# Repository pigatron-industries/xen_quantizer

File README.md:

# Quantizer

A Eurorack quantizer module

[Documentation](https://pigatron-industries.github.io/xen_quantizer/)

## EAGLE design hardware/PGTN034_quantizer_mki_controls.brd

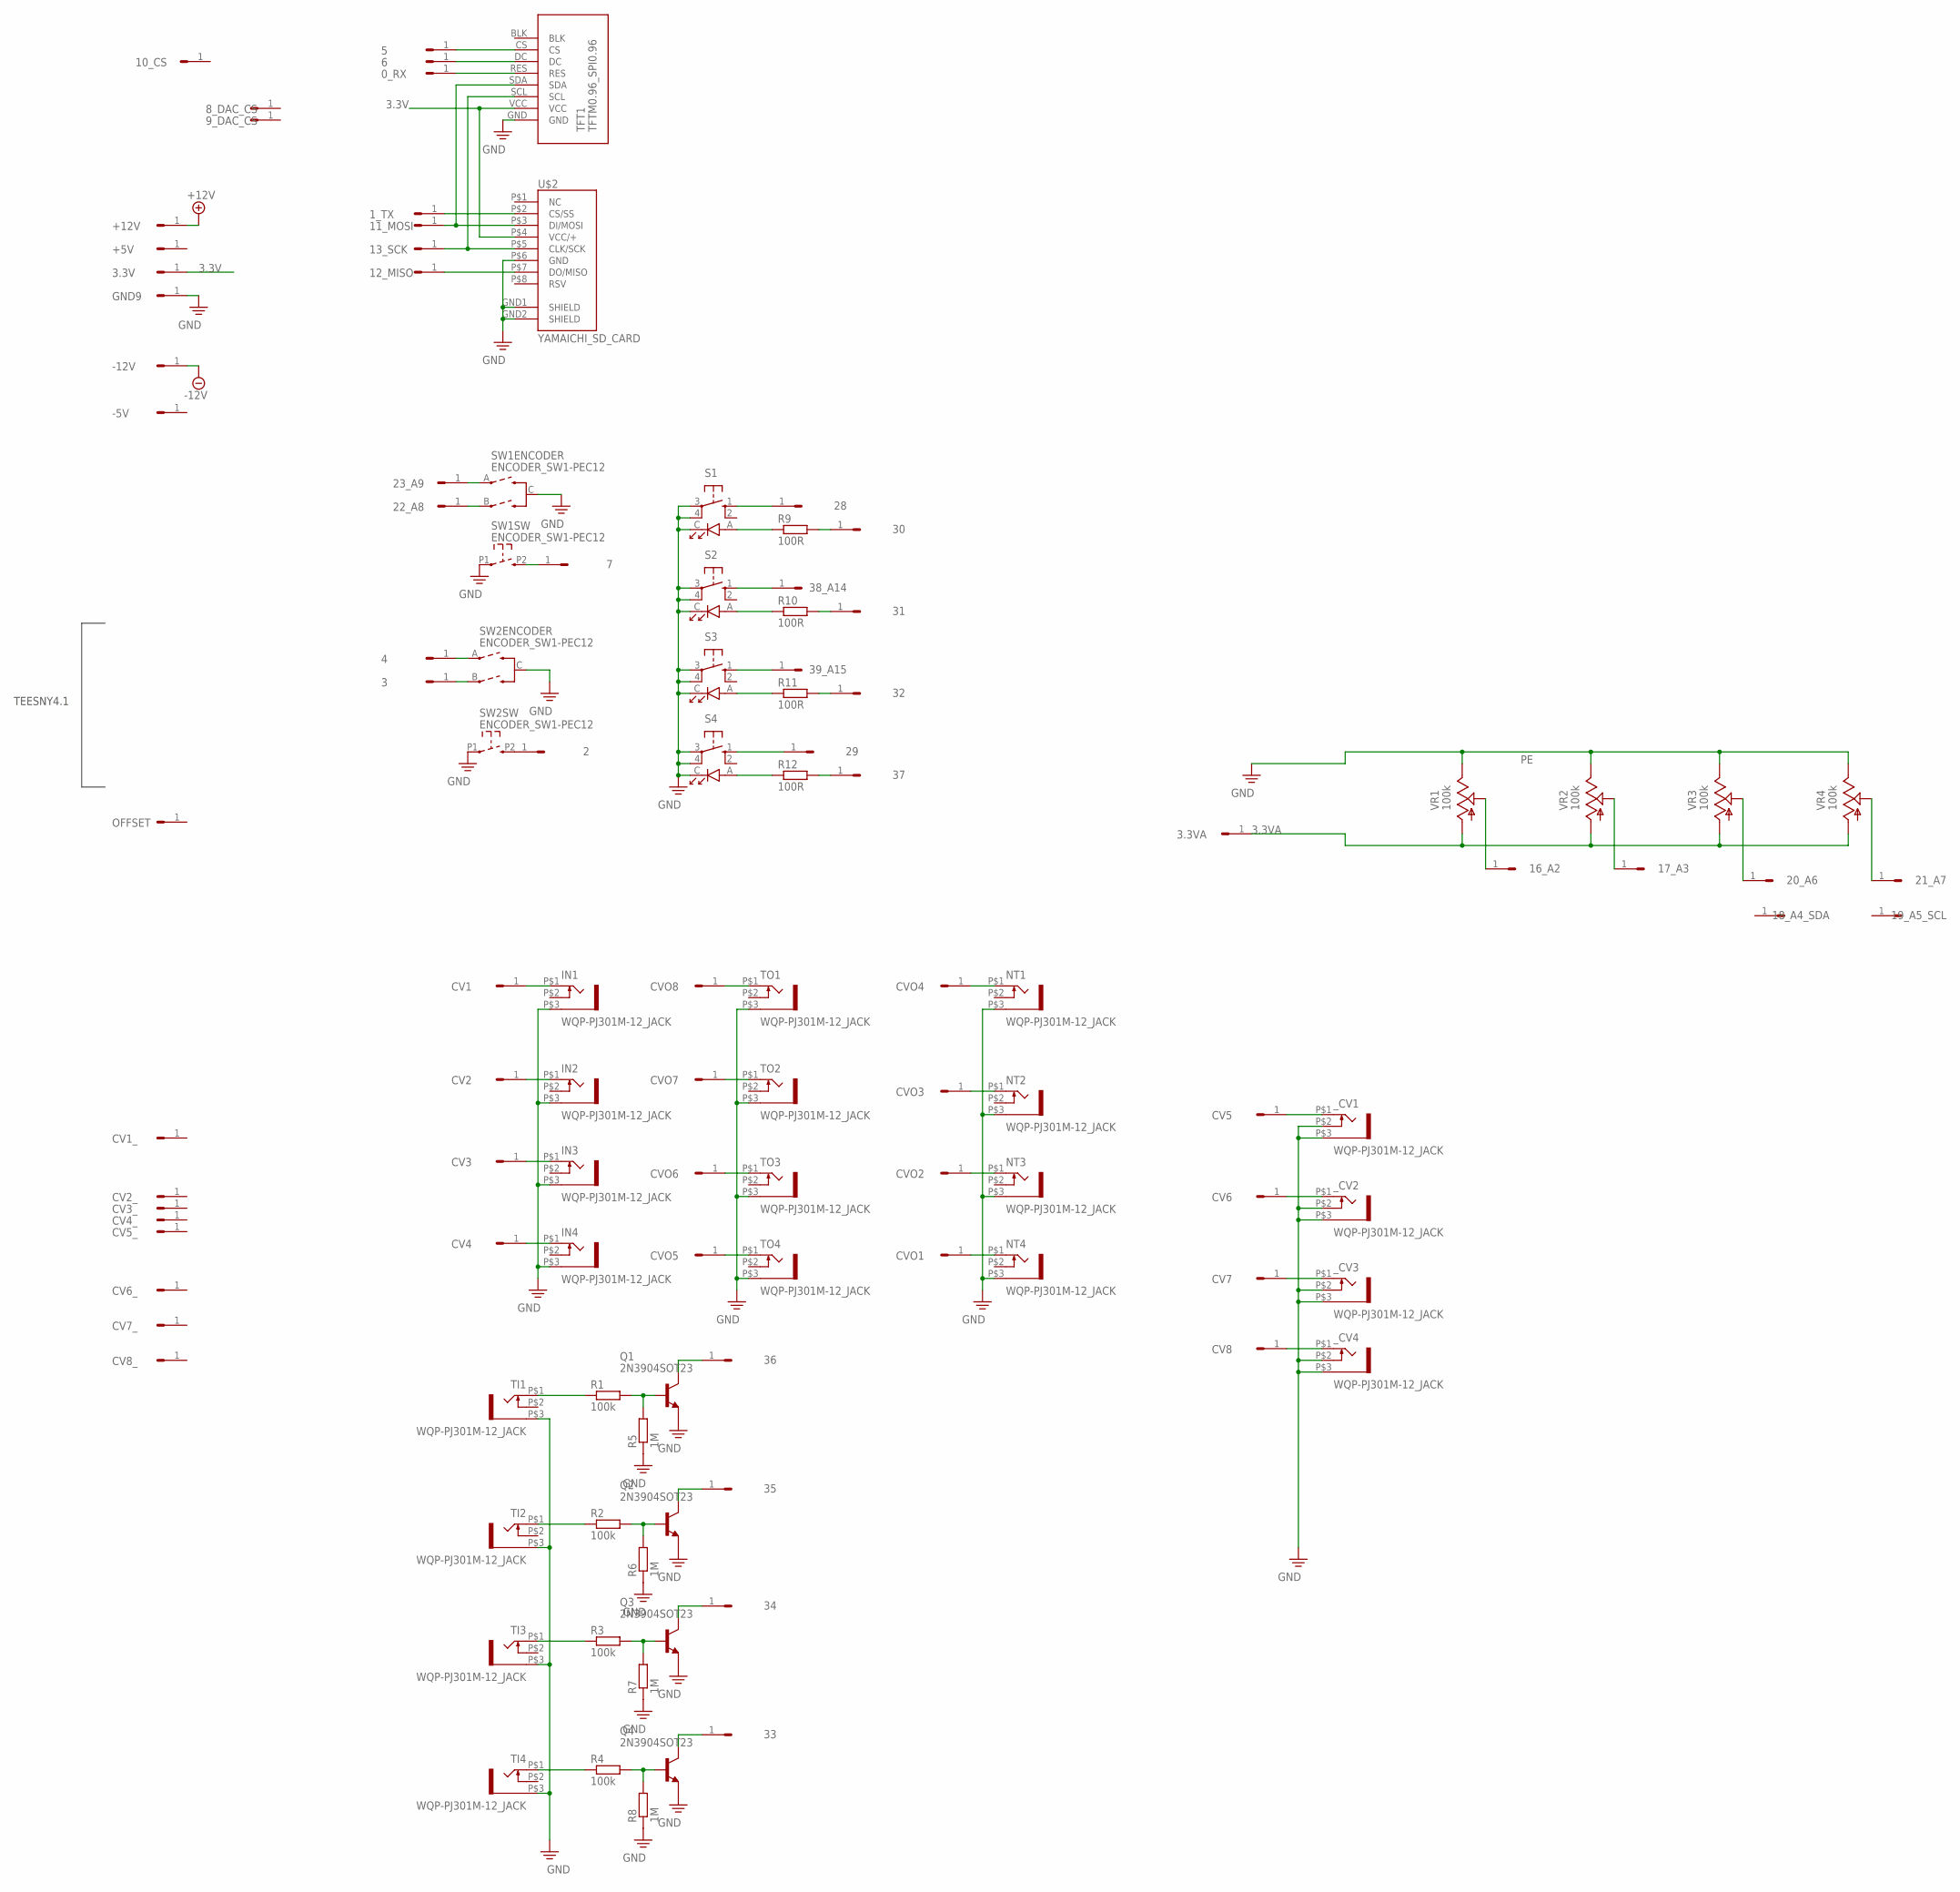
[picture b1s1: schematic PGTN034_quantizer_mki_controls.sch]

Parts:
0_RX, 1_TX, 2, 3, 3.3V, 3.3VA, 4, 5, 6, 7, 8_DAC_CS, 9_DAC_CS, 10_CS, 11_MOSI, 12_MISO, 13_SCK, 16_A2, 17_A3, 18_A4_SDA, 19_A5_SCL, 20_A6, 21_A7, 22_A8, 23_A9, 28, 29, 30, 31, 32, 33, 34, 35, 36, 37, 38_A14, 39_A15: HEADER/MALE/01
+5V, +12V: HEADER/MALE/01
-5V, -12V: HEADER/MALE/01
CV1, CV1_, CV2, CV2_, CV3, CV3_, CV4, CV4_, CV5, CV5_, CV6, CV6_, CV7, CV7_, CV8, CV8_: HEADER/MALE/01
CVO1, CVO2, CVO3, CVO4, CVO5, CVO6, CVO7, CVO8: HEADER/MALE/01
GND9: HEADER/MALE/01
IN1, IN2, IN3, IN4: WQP-PJ301M-12_JACK
NT1, NT2, NT3, NT4: WQP-PJ301M-12_JACK
OFFSET: HEADER/MALE/01
Q1, Q2, Q3, Q4: 2N3904SOT23; SOT23
R1, R2, R3, R4: 100k; R0603
R5, R6, R7, R8: 1M; R0603
R9, R10, R11, R12: 100R; R0603
S1, S2, S3, S4: SW-LEDTHONK; SW-PUSH-TACT-LED-THONK
SW1, SW2: ENCODER_SW1-PEC12; PEC12_INCREMENTAL_ENCODER
TFT1: TFTM0.96_SPI0.96; TFTM0.96
TI1, TI2, TI3, TI4: WQP-PJ301M-12_JACK
TO1, TO2, TO3, TO4: WQP-PJ301M-12_JACK
U$2: YAMAICHI_SD_CARD; YAMAICHI_MICROSD_VERTICAL
VR1, VR2, VR3, VR4: 100k; 9MM_SNAP-IN_POT
_CV1, _CV2, _CV3, _CV4: WQP-PJ301M-12_JACK

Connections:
3.3V: 3.3V.1, TFT1.VCC, U$2.P$4 (VCC/+)
3.3VA: 3.3VA.1, VR1.1 (A), VR2.1 (A), VR3.1 (A), VR4.1 (A)
+12V: +12V.1
-12V: -12V.1
unnamed: CV5.1, _CV1.P$1 (2)
unnamed: 16_A2.1, VR1.2 (S)
unnamed: CV6.1, _CV2.P$1 (2)
unnamed: 0_RX.1, TFT1.RES
unnamed: CVO1.1, NT4.P$1 (2)
unnamed: CVO2.1, NT3.P$1 (2)
unnamed: 17_A3.1, VR2.2 (S)
unnamed: CVO3.1, NT2.P$1 (2)
unnamed: 20_A6.1, VR3.2 (S)
unnamed: 21_A7.1, VR4.2 (S)
unnamed: CVO4.1, NT1.P$1 (2)
unnamed: CVO5.1, TO4.P$1 (2)
unnamed: CVO6.1, TO3.P$1 (2)
unnamed: CVO7.1, TO2.P$1 (2)
unnamed: CVO8.1, TO1.P$1 (2)
unnamed: CV1.1, IN1.P$1 (2)
unnamed: CV2.1, IN2.P$1 (2)
unnamed: CV3.1, IN3.P$1 (2)
unnamed: CV4.1, IN4.P$1 (2)
unnamed: CV7.1, _CV3.P$1 (2)
unnamed: CV8.1, _CV4.P$1 (2)
unnamed: R1.1, TI1.P$1 (2)
unnamed: R2.1, TI2.P$1 (2)
unnamed: R3.1, TI3.P$1 (2)
unnamed: R4.1, TI4.P$1 (2)
unnamed: Q1.1 (B), R1.2, R5.2
unnamed: Q2.1 (B), R2.2, R6.2
unnamed: Q3.1 (B), R3.2, R7.2
unnamed: Q4.1 (B), R4.2, R8.2
unnamed: 36.1, Q1.3 (C)
unnamed: 35.1, Q2.3 (C)
unnamed: 34.1, Q3.3 (C)
unnamed: 33.1, Q4.3 (C)
unnamed: R9.1, S1.A
unnamed: R12.1, S4.A
unnamed: 7.1, SW1.P2 (2)
unnamed: 23_A9.1, SW1.A
unnamed: 22_A8.1, SW1.B
unnamed: R11.1, S3.A
unnamed: R10.1, S2.A
unnamed: 28.1, S1.1 (S)
unnamed: 38_A14.1, S2.1 (S)
unnamed: 39_A15.1, S3.1 (S)
unnamed: 29.1, S4.1 (S)
unnamed: 31.1, R10.2
unnamed: 30.1, R9.2
unnamed: 32.1, R11.2
unnamed: 37.1, R12.2
unnamed: 12_MISO.1, U$2.P$7 (DO/MISO)
unnamed: 11_MOSI.1, TFT1.SDA, U$2.P$3 (DI/MOSI)
unnamed: 13_SCK.1, TFT1.SCL, U$2.P$5 (CLK/SCK)
unnamed: 5.1, TFT1.CS
unnamed: 6.1, TFT1.DC
unnamed: 3.1, SW2.B
unnamed: 4.1, SW2.A
unnamed: 2.1, SW2.P2 (2)
unnamed: 1_TX.1, U$2.P$2 (CS/SS)
PE: GND9.1, IN1.P$3 (1), IN2.P$3 (1), IN3.P$3 (1), IN4.P$3 (1), NT1.P$3 (1), NT2.P$3 (1), NT3.P$3 (1), NT4.P$3 (1), Q1.2 (E), Q2.2 (E), Q3.2 (E), Q4.2 (E), R5.1, R6.1, R7.1, R8.1, S1.3, S1.4 (P1), S1.C, S2.3, S2.4 (P1), S2.C, S3.3, S3.4 (P1), S3.C, S4.3, S4.4 (P1), S4.C, SW1.C, SW1.P1 (1), SW2.C, SW2.P1 (1), TFT1.GND, TI1.P$3 (1), TI2.P$3 (1), TI3.P$3 (1), TI4.P$3 (1), TO1.P$3 (1), TO2.P$3 (1), TO3.P$3 (1), TO4.P$3 (1), U$2.GND1 (SHIELD), U$2.GND2 (SHIELD), U$2.P$6 (GND), VR1.3 (E), VR2.3 (E), VR3.3 (E), VR4.3 (E), _CV1.P$2 (3), _CV1.P$3 (1), _CV2.P$2 (3), _CV2.P$3 (1), _CV3.P$2 (3), _CV3.P$3 (1), _CV4.P$2 (3), _CV4.P$3 (1)

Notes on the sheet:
TEESNY4.1

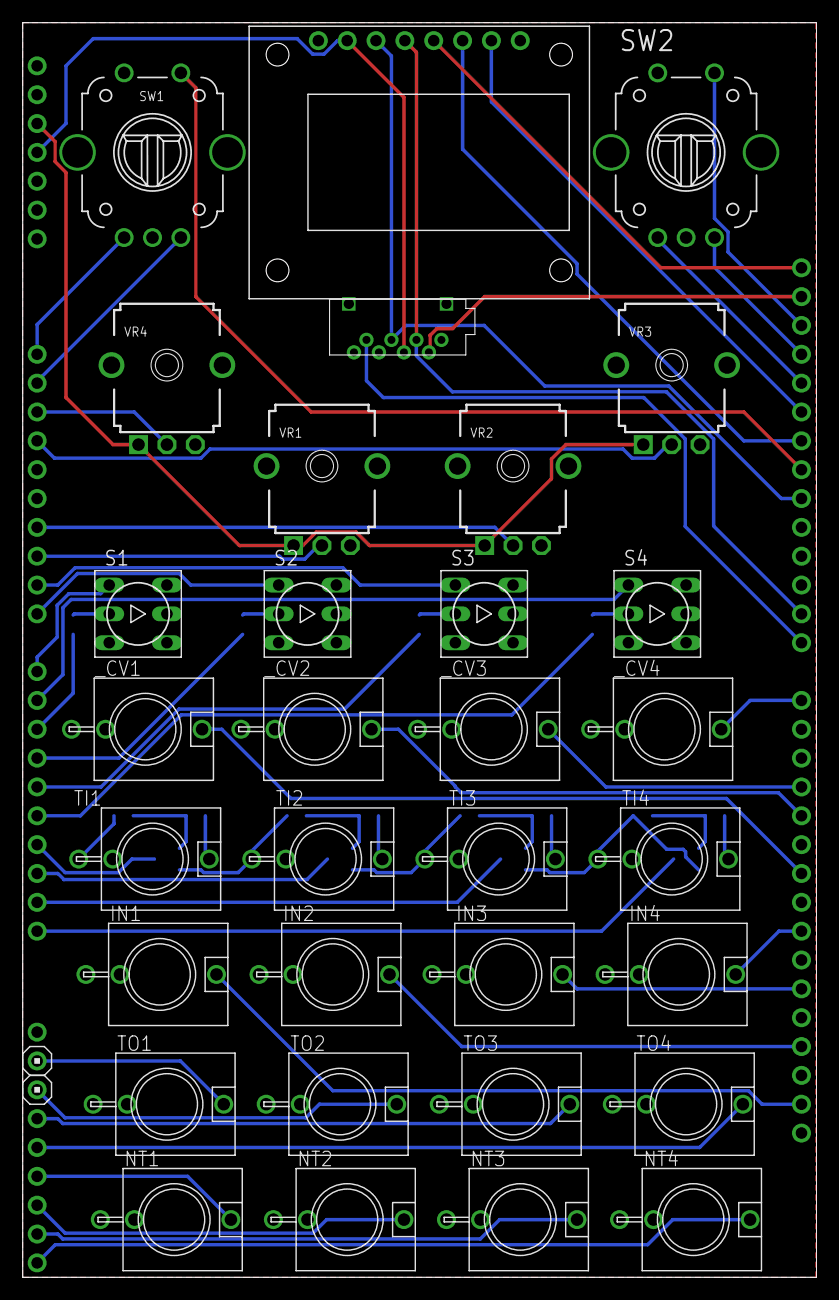
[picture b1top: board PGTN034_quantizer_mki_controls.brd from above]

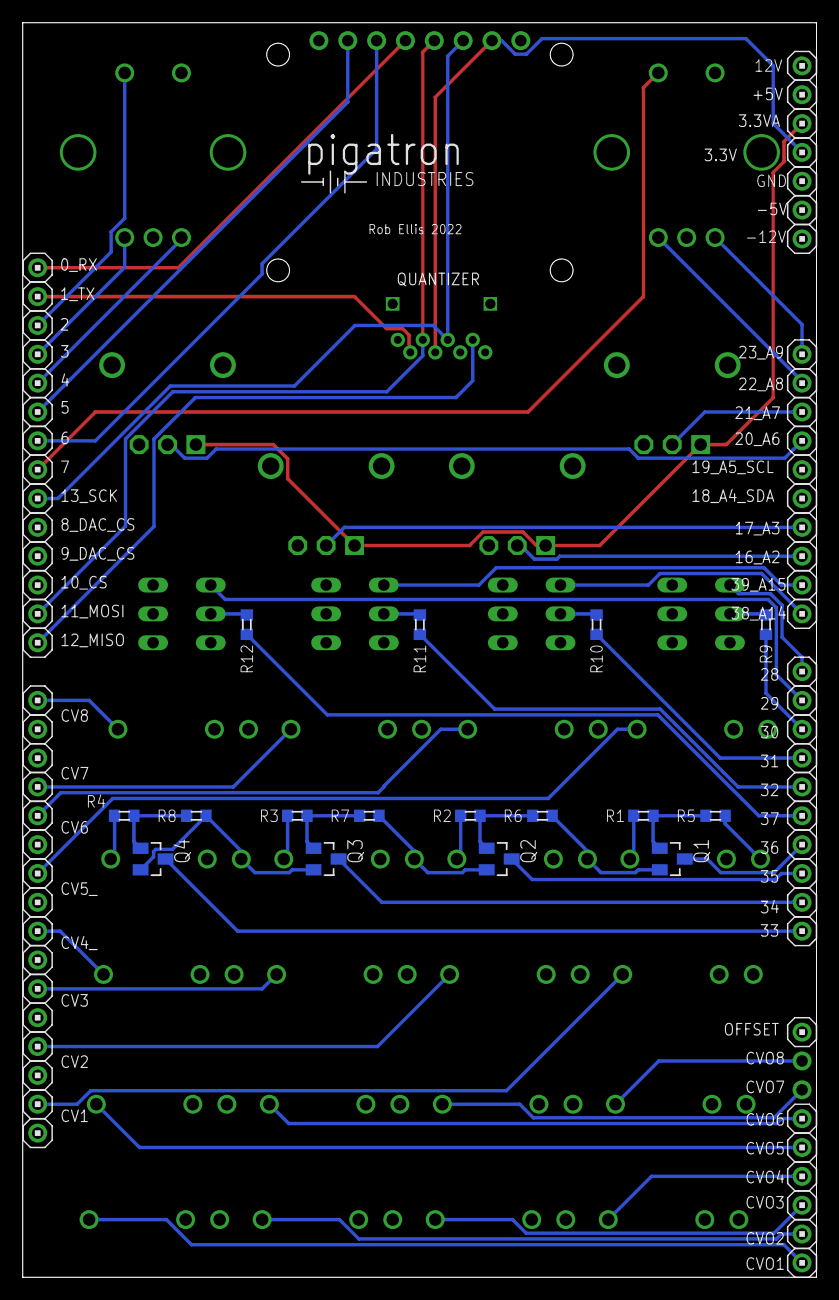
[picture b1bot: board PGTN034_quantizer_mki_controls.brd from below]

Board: 2 copper layers, 69.9 x 110.5 mm, 115 parts (81 on the bottom side), 60 nets.

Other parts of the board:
U$1: PIGATRON-LOGO

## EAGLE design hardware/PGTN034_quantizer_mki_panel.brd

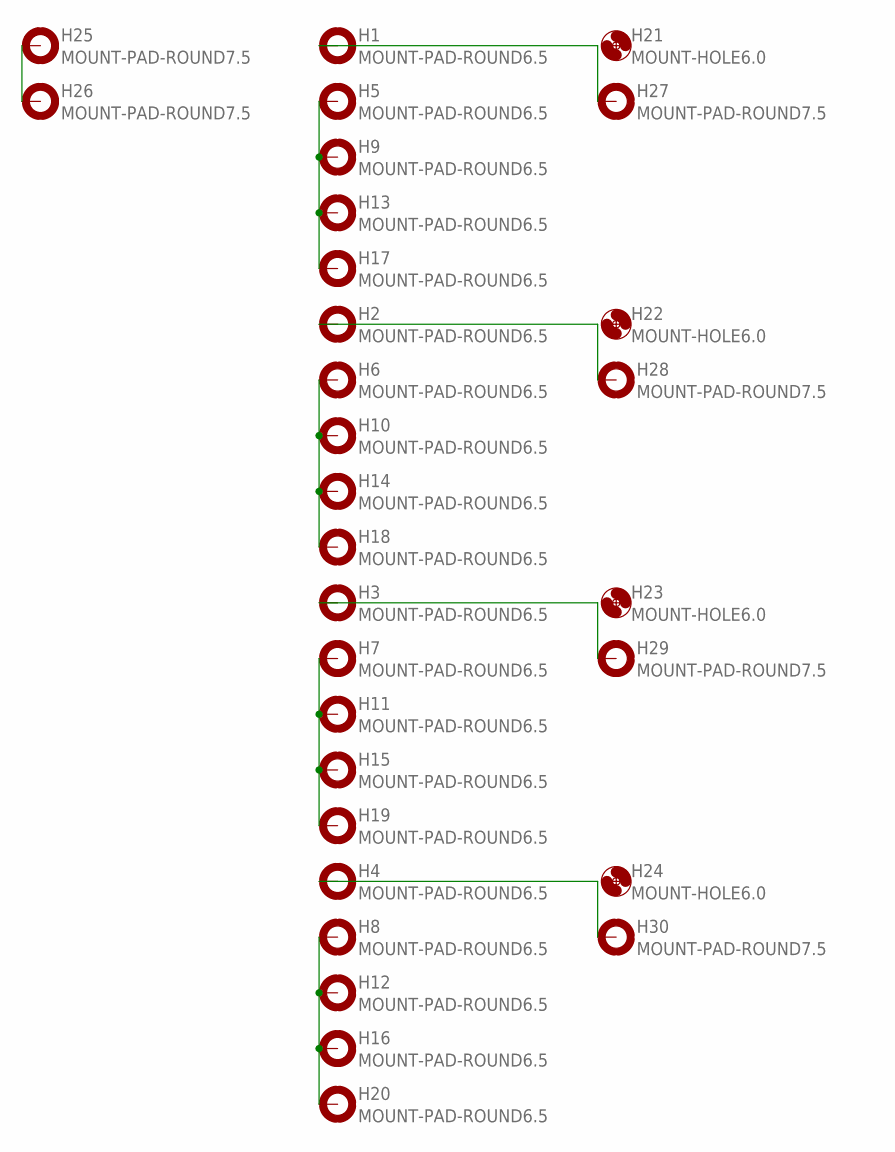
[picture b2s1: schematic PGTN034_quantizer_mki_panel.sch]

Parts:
H1, H2, H3, H4, H5, H6, H7, H8, H9, H10, H11, H12, H13, H14, H15, H16, H17, H18, H19, H20: MOUNT-PAD-ROUND6.5; 6.5-PAD
H21, H22, H23, H24: MOUNT-HOLE6.0; 6,0
H25, H26, H27, H28, H29, H30: MOUNT-PAD-ROUND7.5; 7.5-PAD

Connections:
unnamed: H5.B6.5, H9.B6.5, H13.B6.5, H17.B6.5
unnamed: H6.B6.5, H10.B6.5, H14.B6.5, H18.B6.5
unnamed: H7.B6.5, H11.B6.5, H15.B6.5, H19.B6.5
unnamed: H8.B6.5, H12.B6.5, H16.B6.5, H20.B6.5
unnamed: H2.B6.5, H28.B7.5
unnamed: H3.B6.5, H29.B7.5
unnamed: H4.B6.5, H30.B7.5
unnamed: H25.B7.5, H26.B7.5
unnamed: H1.B6.5, H27.B7.5

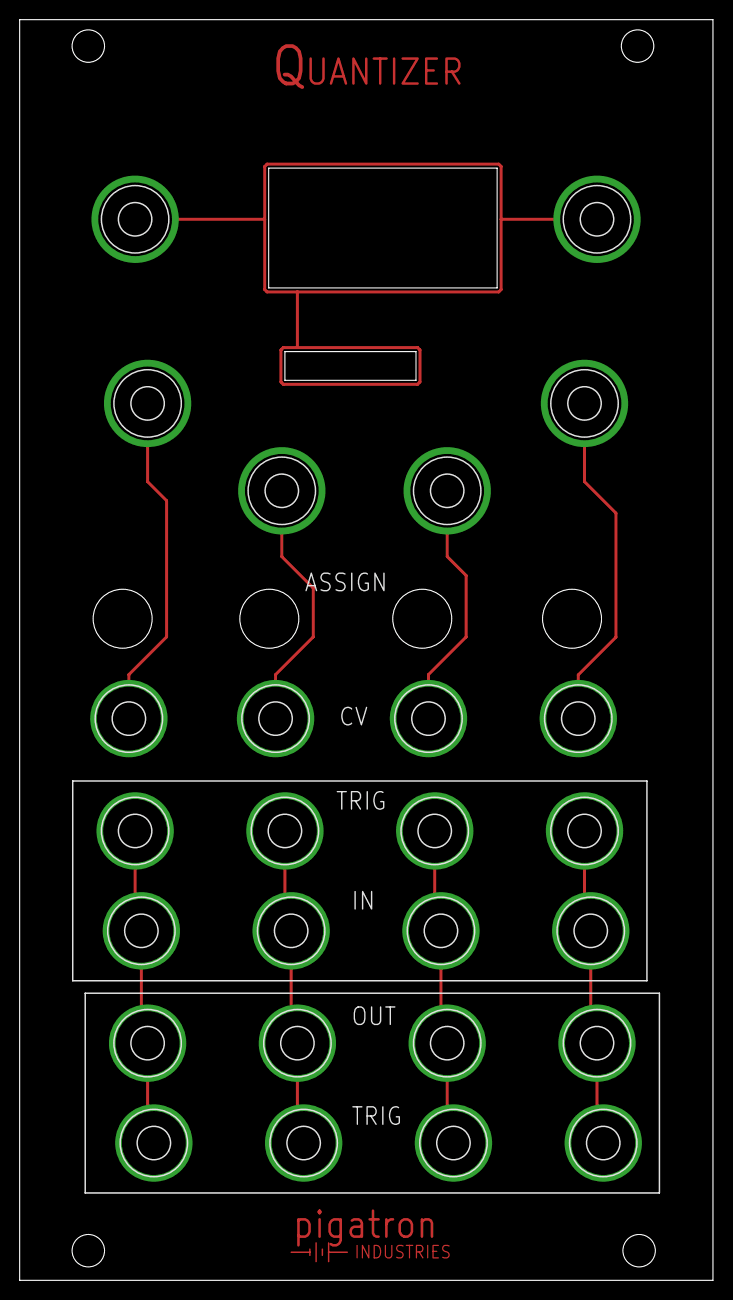
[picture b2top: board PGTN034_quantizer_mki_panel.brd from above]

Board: 2 copper layers, 70.5 x 128.3 mm, 35 parts (0 on the bottom side), 9 nets.

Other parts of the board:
U$2: PIGATRON-LOGO-TRACE
U$3, U$4, U$5, U$6: 3,3

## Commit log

2022-04-25 initial code commit
2022-04-26 hardware and controller
2022-04-26 re-order pins + add MCP23S17
2022-04-29 Pitch quantizer
2022-05-01 add library.json to use as library
2022-05-01 added tuning
2022-05-01 rename to tuning
2022-05-01 correct srcDir
2022-05-01 name changes
2022-05-01 Removed note from quantizer
2022-05-02 Renamed some types
2022-05-03 scale repository
2022-05-04 manage links between scales and chords
2022-05-07 Tuning mode to help with oscilaltor tuning
2022-05-07 ignore compiled python files
2022-05-10 Python code to visualise scales
2022-05-12 rename
2022-05-12 plot notes
2022-05-13 repeat modes and scales
2022-05-13 More text
2022-05-13 convert script
2022-05-13 use mathjax
2022-05-20 Added polar plots
2022-05-20 Added polar plots of scales and chords
2022-05-21 Chord quality selected by scale
2022-05-21 Scale offset pot
2022-05-22 Fixed quantizer bugs and added tests
2022-05-23 added chord tests
2022-05-23 Fix offset scale chords
2022-05-24 title
2022-05-26 Simplified scale offsets
2022-05-27 moved py files to lib folder
2022-05-27 clear outputs
2022-05-27 harmonics
2022-05-27 harmonics plot changes
2022-05-28 rename PitchQuantizer
2022-05-29 python changes
2022-05-29 Quantize to current chord
2022-05-29 set chord in init
2022-05-31 add dissonance rating to intervals
2022-06-01 Add offset in quantizeToChord
2022-06-04 Refactor
2022-06-05 Moved tuning data out of controllers
2022-06-07 chord defs stored in scales
2022-06-09 Add chromatic scales and chord qualities
2022-06-10 fix tests
2022-06-11 Select chord type via pot
2022-06-18 load tunings from sd card
2022-06-18 Select scales and tunings with encoder
2022-07-31 Changed encoder and trigger input pins
2022-07-31 updated hardware pins
2022-08-04 add display lib
2022-08-04 Add graphics classes
2022-08-05 Calibration
2022-08-05 field component
2022-08-05 Fixed SPI interrupt clash
2022-08-06 Added calibration interface
2022-08-06 Quantizer interface
2022-08-06 Zero outputs on calibration
2022-08-07 Add chord quality parameter
2022-08-12 note visualisation
2022-08-12 implement 2 encoder control scheme
2022-08-13 Clear tunings before loading
2022-08-13 Scale offset parameter
2022-08-13 Add chord to interface
2022-08-13 Ignore comments in file
2022-08-14 tidy up
2022-08-14 Fix issue with changing tuning
2022-08-14 Loading message
2022-08-15 text
2022-08-20 Moved graphics code to library
2022-09-12 removed commented out line
2022-09-12 Add SPI SD Card
2022-09-20 set offset when changing scale
2022-09-20 move methods to abstract controller
2023-05-28 add sequencer controller
2023-06-18 experimental neural sequencer
2023-06-19 load metadata
2023-06-23 correct return type
2023-06-23 remove include flags
2023-06-23 remove math library included in tflite library
2023-06-27 run inference and output note voltages
2023-07-08 use external PSRAM chip for bigger models
2023-07-09 add reset trigger input for sequencer
2023-07-14 Use double encoder controller from library
2023-07-14 implement new controller type
2023-07-19 use parameterized controller from lib
2023-07-19 exclude neural from lib
2023-07-21 save paramters to eeprom
2023-07-22 implement model changing
2023-07-28 split drum and note decoders into seperate controllers
2023-08-08 moved trigger outputs to subclass
2023-08-08 use arrays for notes and percussion groups
2023-08-12 add percussion group information to metadata
2023-08-12 add name to model
2023-08-20 handle no model on sd card
2023-08-20 harmonic walk controller
2023-08-20 read file with tuning specified in ratios
2023-10-01 calibration insterface
2023-10-20 move tick counting to controller
2023-10-21 sequence visualiser
2023-10-21 show sequence on display
2023-10-22 docs
2023-10-22 common docs submodule
2023-10-22 crop
2023-10-22 typo
2023-10-22 add current sequence position to ui
2023-10-22 enable manual and externally triggered inference
2023-10-28 add bill of materials
2023-10-29 display scale and offset while calibrating
2023-11-11 differnet colouring modes for drums and notes
2023-11-12 make output triggers / cv consistent between controllers
2023-11-12 midi input mode
2023-11-27 don't load tuning file until it has been manually selected
2023-12-09 clear interface tick on sequence reset
2023-12-09 fix ratio file reading goign to wrong interval number
2023-12-09 change output pins of harmonic walk
2023-12-10 control interval selection with cv
2023-12-10 documentation for generative decoder
2023-12-10 black line
2023-12-10 add clock pause function
2023-12-11 add sentences
2023-12-31 fix chord quantizer issue
2024-01-14 calibration UI changes
2024-03-23 remove ObjectManager
2024-03-23 add mempool to add method of LinkedList
2024-03-30 add midi slave mode
2024-03-31 library updates
2024-04-14 add sd card reader and spacers to bom
2024-04-14 correct OLED spec
2024-04-14 add build guide
2024-04-14 remove file
2024-04-26 19edo
2024-04-26 offset cv and pot
2024-04-27 offset to scale notes
2024-04-29 add 19 edo tuning info
2024-04-29 create scale from steps
2024-04-29 support non octave scale plots
2024-05-01 scale generator
2024-05-05 read/write from mutliple midi devices
2024-05-06 select tuning in midi mode
2024-05-06 midi channel configuration
2024-05-06 manual reset
2024-05-19 allow quantizer outputs to be fixed to chord or free
2024-05-26 allow quantization to be disabled with gate input
2024-05-27 sequencer controller
2024-05-27 13EDT
2024-05-27 isomorphic keyboard layouts
2024-05-31 update image
2024-05-31 update manual
2024-05-31 add doc link
2024-05-31 add header
2024-06-01 rotate midi outputs
2024-06-01 allow all midi channels to output notes
2024-06-04 scale info
2024-06-04 pitch bend and rpn parameters
2024-06-08 output rotation option
2024-06-10 sequencer
2024-06-10 add layouts
2024-06-12 access midicontroller from sequencer
2024-06-15 fix MidiController instance
2024-06-16 midi input in sequencer
2024-06-16 rotation fix
2024-06-22 Add multiple patterns to sequencer
2024-07-08 ssequence recording improvements
2024-07-08 keyboard orientation
